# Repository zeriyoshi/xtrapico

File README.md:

# xtrapico
Double sided extra small footprint RP2040 implementation, Forcus on [JLCPCB](https://jlcpcb.com/).

Schma based by [22008-RP2040-Dev-Board](https://github.com/Breadstick-Innovations/22008-RP2040-Dev-Board)

# License
MIT

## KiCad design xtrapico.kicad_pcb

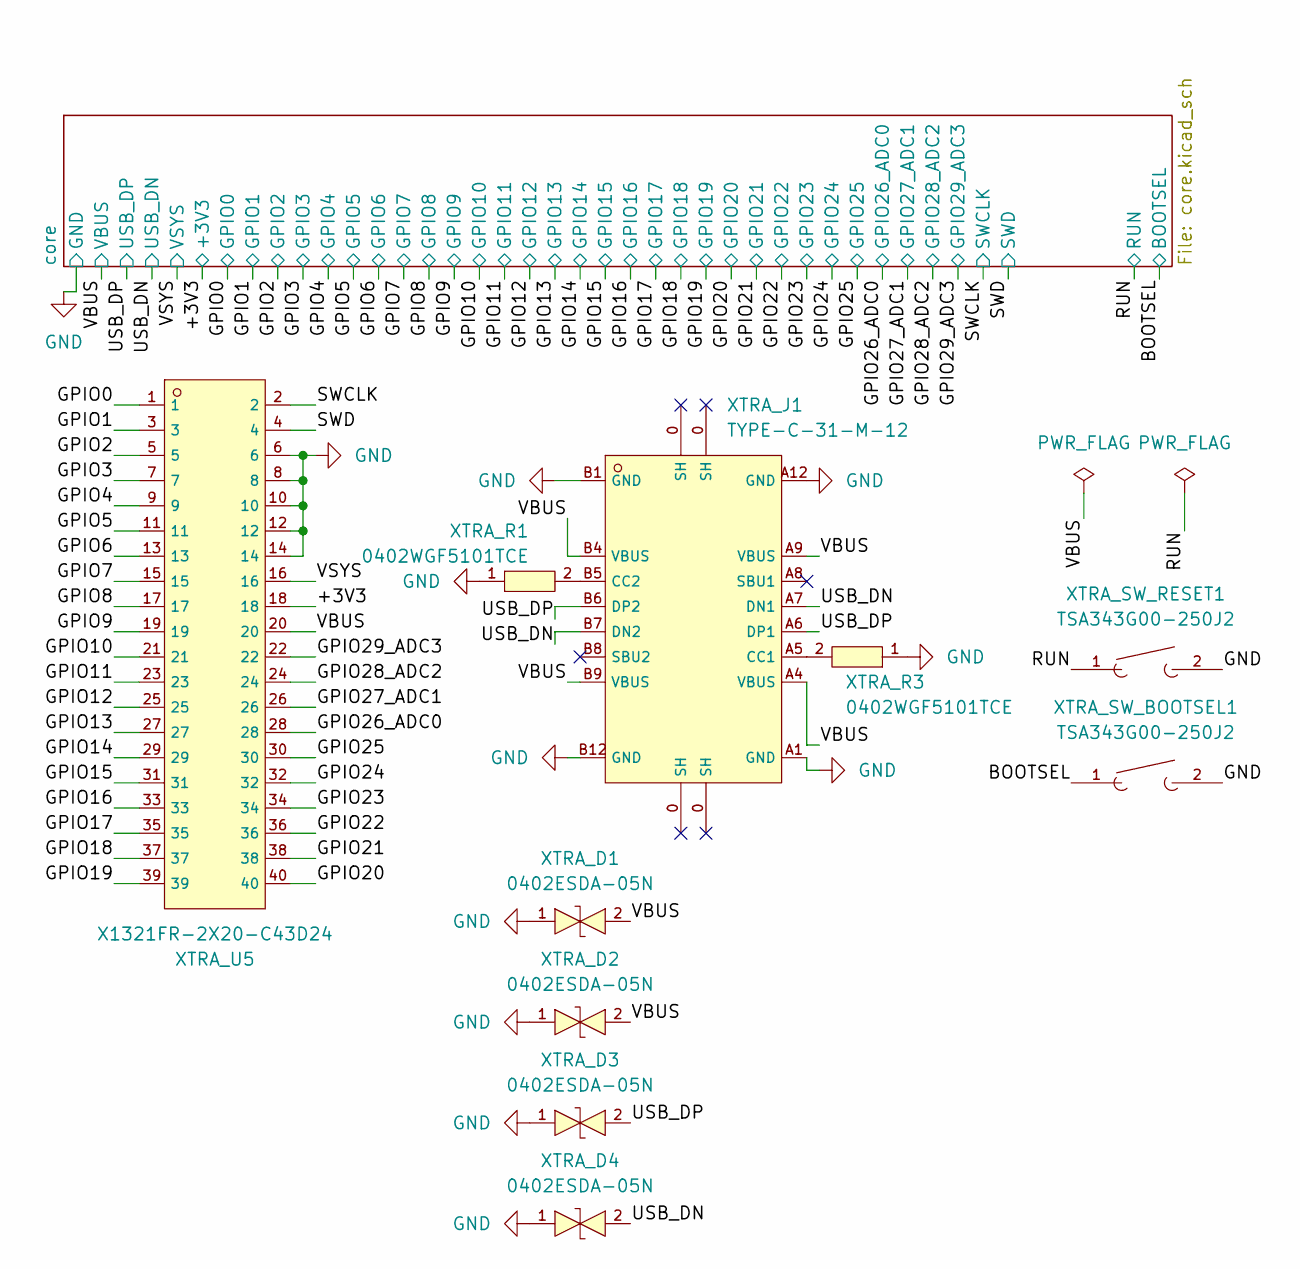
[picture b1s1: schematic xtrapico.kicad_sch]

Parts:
XTRA_D1, XTRA_D2, XTRA_D3, XTRA_D4: 0402ESDA-05N; D0402-BI; LCSC C316049
XTRA_J1: TYPE-C-31-M-12; USB-C_SMD-TYPE-C-31-M-12; LCSC C165948
XTRA_R1, XTRA_R3: 0402WGF5101TCE; R0402; LCSC C25905
XTRA_SW_BOOTSEL1: TSA343G00-250J2; SW-SMD_L4.0-W2.9-LS5.0; LCSC C354946
XTRA_SW_RESET1: TSA343G00-250J2; SW-SMD_L4.0-W2.9-LS5.0; LCSC C354946
XTRA_U5: X1321FR-2X20-C43D24; CONN-TH_40P_X1321FR-2X20-C43D24; LCSC C2881906

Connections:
/+3V3: XTRA_U5.18; also elsewhere on the board
/BOOTSEL: XTRA_SW_BOOTSEL1.1; also elsewhere on the board
/GPIO0: XTRA_U5.1; also elsewhere on the board
/GPIO1: XTRA_U5.3; also elsewhere on the board
/GPIO2: XTRA_U5.5; also elsewhere on the board
/GPIO3: XTRA_U5.7; also elsewhere on the board
/GPIO4: XTRA_U5.9; also elsewhere on the board
/GPIO5: XTRA_U5.11; also elsewhere on the board
/GPIO6: XTRA_U5.13; also elsewhere on the board
/GPIO7: XTRA_U5.15; also elsewhere on the board
/GPIO8: XTRA_U5.17; also elsewhere on the board
/GPIO9: XTRA_U5.19; also elsewhere on the board
/GPIO10: XTRA_U5.21; also elsewhere on the board
/GPIO11: XTRA_U5.23; also elsewhere on the board
/GPIO12: XTRA_U5.25; also elsewhere on the board
/GPIO13: XTRA_U5.27; also elsewhere on the board
/GPIO14: XTRA_U5.29; also elsewhere on the board
/GPIO15: XTRA_U5.31; also elsewhere on the board
/GPIO16: XTRA_U5.33; also elsewhere on the board
/GPIO17: XTRA_U5.35; also elsewhere on the board
/GPIO18: XTRA_U5.37; also elsewhere on the board
/GPIO19: XTRA_U5.39; also elsewhere on the board
/GPIO20: XTRA_U5.40; also elsewhere on the board
/GPIO21: XTRA_U5.38; also elsewhere on the board
/GPIO22: XTRA_U5.36; also elsewhere on the board
/GPIO23: XTRA_U5.34; also elsewhere on the board
/GPIO24: XTRA_U5.32; also elsewhere on the board
/GPIO25: XTRA_U5.30; also elsewhere on the board
/GPIO26_ADC0: XTRA_U5.28; also elsewhere on the board
/GPIO27_ADC1: XTRA_U5.26; also elsewhere on the board
/GPIO28_ADC2: XTRA_U5.24; also elsewhere on the board
/GPIO29_ADC3: XTRA_U5.22; also elsewhere on the board
/RUN: XTRA_SW_RESET1.1; also elsewhere on the board
/SWCLK: XTRA_U5.2; also elsewhere on the board
/SWD: XTRA_U5.4; also elsewhere on the board
/USB_DN: XTRA_D4.2, XTRA_J1.A7 (DN1), XTRA_J1.B7 (DN2); also elsewhere on the board
/USB_DP: XTRA_D3.2, XTRA_J1.A6 (DP1), XTRA_J1.B6 (DP2); also elsewhere on the board
/VBUS: XTRA_D1.2, XTRA_D2.2, XTRA_J1.A4 (VBUS), XTRA_J1.A9 (VBUS), XTRA_J1.B4 (VBUS), XTRA_J1.B9 (VBUS), XTRA_U5.20; also elsewhere on the board
/VSYS: XTRA_U5.16; also elsewhere on the board
GND: XTRA_D1.1, XTRA_D2.1, XTRA_D3.1, XTRA_D4.1, XTRA_J1.A1 (GND), XTRA_J1.A12 (GND), XTRA_J1.B1 (GND), XTRA_J1.B12 (GND), XTRA_R1.1, XTRA_R3.1, XTRA_SW_BOOTSEL1.2, XTRA_SW_RESET1.2, XTRA_U5.6, XTRA_U5.8, XTRA_U5.10, XTRA_U5.12, XTRA_U5.14; also elsewhere on the board
unnamed: XTRA_J1.A5 (CC1), XTRA_R3.2
unnamed: XTRA_J1.B5 (CC2), XTRA_R1.2

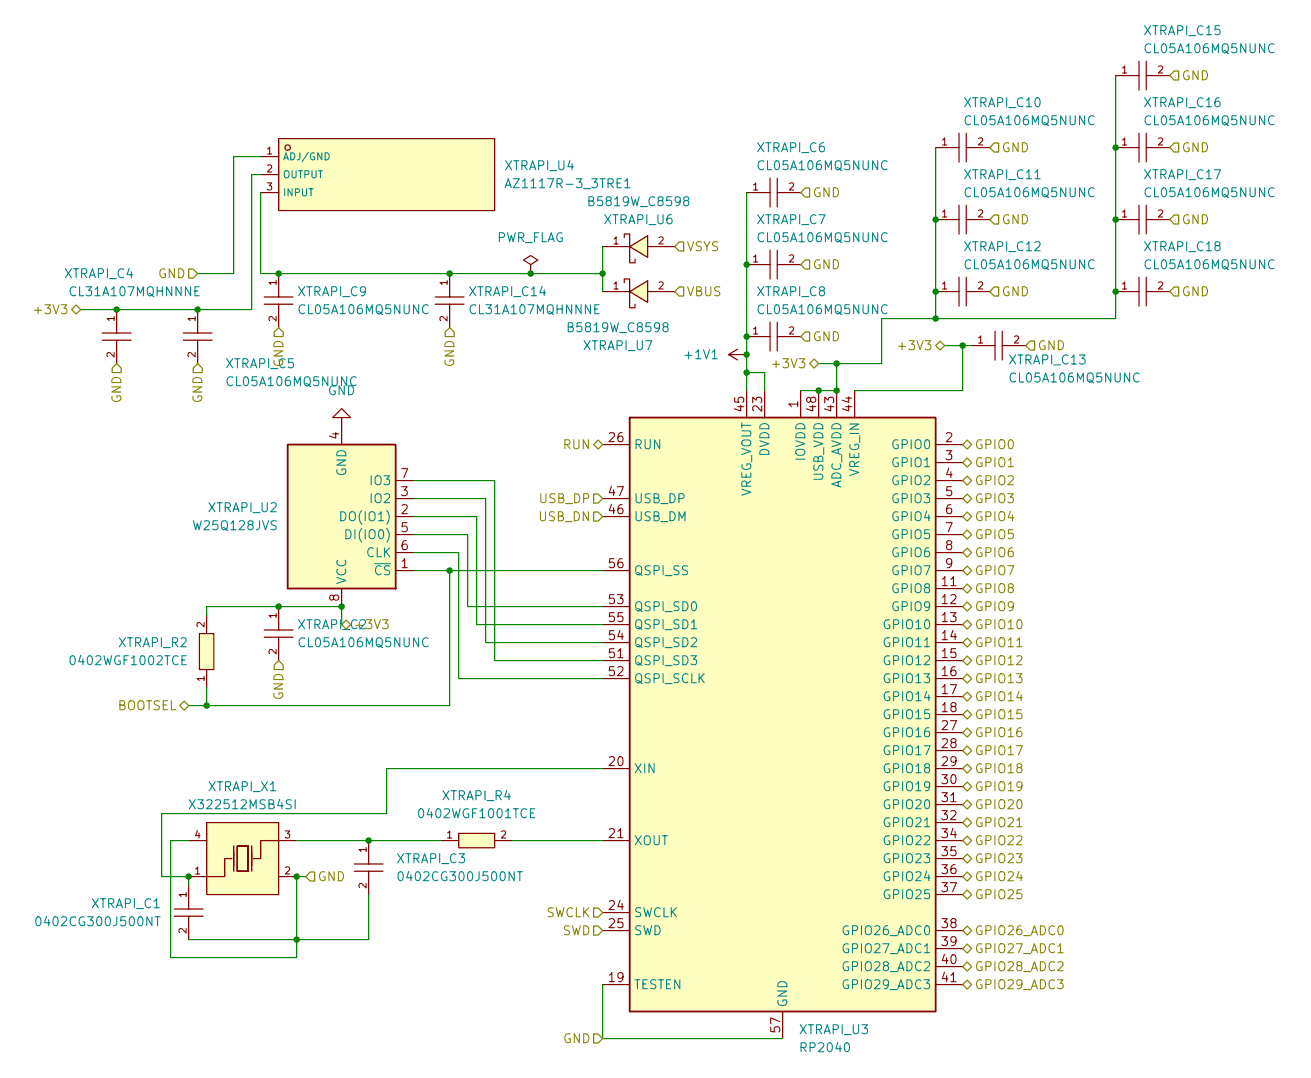
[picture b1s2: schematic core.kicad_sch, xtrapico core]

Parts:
XTRAPI_C1, XTRAPI_C3: 0402CG300J500NT; C0402; LCSC C1570
XTRAPI_C2, XTRAPI_C5, XTRAPI_C6, XTRAPI_C7, XTRAPI_C8, XTRAPI_C9, XTRAPI_C10, XTRAPI_C11, XTRAPI_C12, XTRAPI_C13, XTRAPI_C15, XTRAPI_C16, XTRAPI_C17, XTRAPI_C18: CL05A106MQ5NUNC; C0402; LCSC C15525
XTRAPI_C4, XTRAPI_C14: CL31A107MQHNNNE; C1206; LCSC C15008
XTRAPI_R2: 0402WGF1002TCE; R0402; LCSC C25744
XTRAPI_R4: 0402WGF1001TCE; R0402; LCSC C11702
XTRAPI_U2: W25Q128JVS; SOIC-8_5.23x5.23mm_P1.27mm
XTRAPI_U3: RP2040; QFN-56-1EP_7x7mm_P0.4mm_EP3.2x3.2mm
XTRAPI_U4: AZ1117R-3_3TRE1; SOT-89-3_L4.5-W2.5-P1.50-LS4.2-BR; LCSC C108493
XTRAPI_U6, XTRAPI_U7: B5819W_C8598; SOD-123_L2.7-W1.6-LS3.7-RD-1; LCSC C8598
XTRAPI_X1: X322512MSB4SI; OSC-SMD_4P-L3.2-W2.5-BL; LCSC C9002

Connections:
+1V1: XTRAPI_C6.1, XTRAPI_C7.1, XTRAPI_C8.1, XTRAPI_U3.23 (DVDD), XTRAPI_U3.45 (VREG_VOUT), XTRAPI_U3.50 (DVDD)
/+3V3: XTRAPI_C2.1, XTRAPI_C4.1, XTRAPI_C5.1, XTRAPI_C10.1, XTRAPI_C11.1, XTRAPI_C12.1, XTRAPI_C13.1, XTRAPI_C15.1, XTRAPI_C16.1, XTRAPI_C17.1, XTRAPI_C18.1, XTRAPI_R2.2, XTRAPI_U2.8 (VCC), XTRAPI_U3.1 (IOVDD), XTRAPI_U3.10 (IOVDD), XTRAPI_U3.22 (IOVDD), XTRAPI_U3.33 (IOVDD), XTRAPI_U3.42 (IOVDD), XTRAPI_U3.43 (ADC_AVDD), XTRAPI_U3.44 (VREG_IN), XTRAPI_U3.48 (USB_VDD), XTRAPI_U3.49 (IOVDD), XTRAPI_U4.2 (OUTPUT); also elsewhere on the board
/BOOTSEL: XTRAPI_R2.1, XTRAPI_U2.1 (~CS), XTRAPI_U3.56 (QSPI_SS); also elsewhere on the board
/GPIO0: XTRAPI_U3.2 (GPIO0); also elsewhere on the board
/GPIO1: XTRAPI_U3.3 (GPIO1); also elsewhere on the board
/GPIO2: XTRAPI_U3.4 (GPIO2); also elsewhere on the board
/GPIO3: XTRAPI_U3.5 (GPIO3); also elsewhere on the board
/GPIO4: XTRAPI_U3.6 (GPIO4); also elsewhere on the board
/GPIO5: XTRAPI_U3.7 (GPIO5); also elsewhere on the board
/GPIO6: XTRAPI_U3.8 (GPIO6); also elsewhere on the board
/GPIO7: XTRAPI_U3.9 (GPIO7); also elsewhere on the board
/GPIO8: XTRAPI_U3.11 (GPIO8); also elsewhere on the board
/GPIO9: XTRAPI_U3.12 (GPIO9); also elsewhere on the board
/GPIO10: XTRAPI_U3.13 (GPIO10); also elsewhere on the board
/GPIO11: XTRAPI_U3.14 (GPIO11); also elsewhere on the board
/GPIO12: XTRAPI_U3.15 (GPIO12); also elsewhere on the board
/GPIO13: XTRAPI_U3.16 (GPIO13); also elsewhere on the board
/GPIO14: XTRAPI_U3.17 (GPIO14); also elsewhere on the board
/GPIO15: XTRAPI_U3.18 (GPIO15); also elsewhere on the board
/GPIO16: XTRAPI_U3.27 (GPIO16); also elsewhere on the board
/GPIO17: XTRAPI_U3.28 (GPIO17); also elsewhere on the board
/GPIO18: XTRAPI_U3.29 (GPIO18); also elsewhere on the board
/GPIO19: XTRAPI_U3.30 (GPIO19); also elsewhere on the board
/GPIO20: XTRAPI_U3.31 (GPIO20); also elsewhere on the board
/GPIO21: XTRAPI_U3.32 (GPIO21); also elsewhere on the board
/GPIO22: XTRAPI_U3.34 (GPIO22); also elsewhere on the board
/GPIO23: XTRAPI_U3.35 (GPIO23); also elsewhere on the board
/GPIO24: XTRAPI_U3.36 (GPIO24); also elsewhere on the board
/GPIO25: XTRAPI_U3.37 (GPIO25); also elsewhere on the board
/GPIO26_ADC0: XTRAPI_U3.38 (GPIO26_ADC0); also elsewhere on the board
/GPIO27_ADC1: XTRAPI_U3.39 (GPIO27_ADC1); also elsewhere on the board
/GPIO28_ADC2: XTRAPI_U3.40 (GPIO28_ADC2); also elsewhere on the board
/GPIO29_ADC3: XTRAPI_U3.41 (GPIO29_ADC3); also elsewhere on the board
/RUN: XTRAPI_U3.26 (RUN); also elsewhere on the board
/SWCLK: XTRAPI_U3.24 (SWCLK); also elsewhere on the board
/SWD: XTRAPI_U3.25 (SWD); also elsewhere on the board
/USB_DN: XTRAPI_U3.46 (USB_DM); also elsewhere on the board
/USB_DP: XTRAPI_U3.47 (USB_DP); also elsewhere on the board
/VBUS: XTRAPI_U7.2 (+); also elsewhere on the board
/VSYS: XTRAPI_U6.2 (+); also elsewhere on the board
GND: XTRAPI_C1.2, XTRAPI_C2.2, XTRAPI_C3.2, XTRAPI_C4.2, XTRAPI_C5.2, XTRAPI_C6.2, XTRAPI_C7.2, XTRAPI_C8.2, XTRAPI_C9.2, XTRAPI_C10.2, XTRAPI_C11.2, XTRAPI_C12.2, XTRAPI_C13.2, XTRAPI_C14.2, XTRAPI_C15.2, XTRAPI_C16.2, XTRAPI_C17.2, XTRAPI_C18.2, XTRAPI_U2.4 (GND), XTRAPI_U3.19 (TESTEN), XTRAPI_U3.57 (GND), XTRAPI_U4.1 (ADJ/GND), XTRAPI_X1.2 (GND), XTRAPI_X1.4 (GND); also elsewhere on the board
unnamed: XTRAPI_U2.6 (CLK), XTRAPI_U3.52 (QSPI_SCLK)
unnamed: XTRAPI_U2.5 (DI(IO0)), XTRAPI_U3.53 (QSPI_SD0)
unnamed: XTRAPI_U2.2 (DO(IO1)), XTRAPI_U3.55 (QSPI_SD1)
unnamed: XTRAPI_U2.3 (IO2), XTRAPI_U3.54 (QSPI_SD2)
unnamed: XTRAPI_U2.7 (IO3), XTRAPI_U3.51 (QSPI_SD3)
unnamed: XTRAPI_C1.1, XTRAPI_U3.20 (XIN), XTRAPI_X1.1 (OSC1)
unnamed: XTRAPI_R4.2, XTRAPI_U3.21 (XOUT)
unnamed: XTRAPI_C9.1, XTRAPI_C14.1, XTRAPI_U4.3 (INPUT), XTRAPI_U6.1 (-), XTRAPI_U7.1 (-)
unnamed: XTRAPI_C3.1, XTRAPI_R4.1, XTRAPI_X1.3 (OSC2)

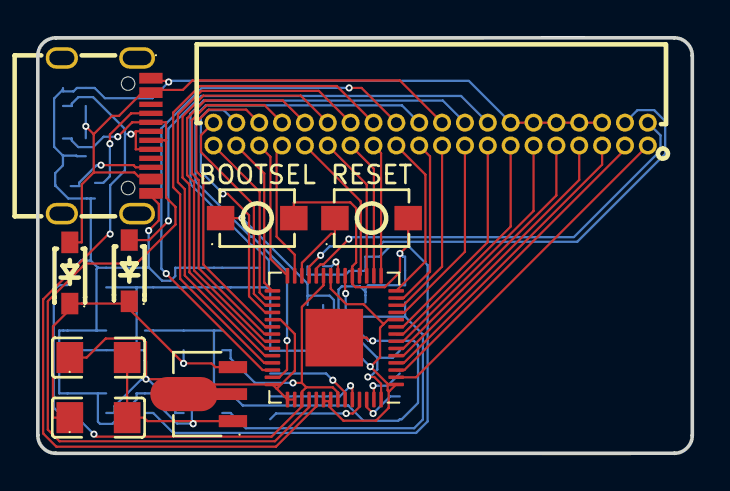
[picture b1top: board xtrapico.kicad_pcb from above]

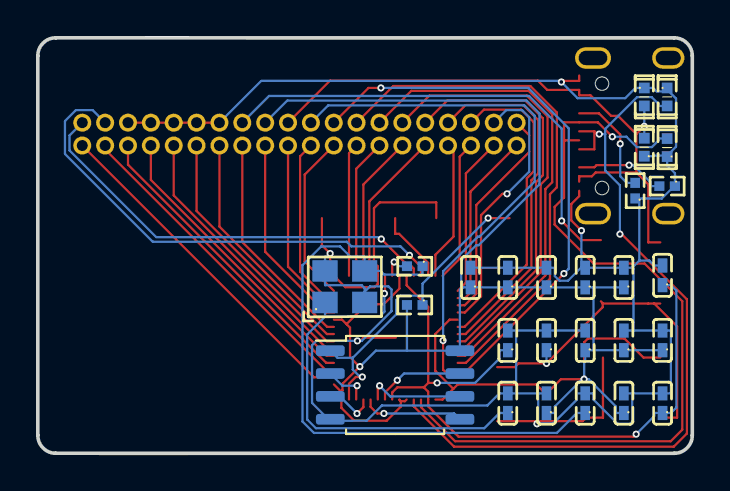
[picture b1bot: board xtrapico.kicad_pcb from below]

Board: 2 copper layers, 36.4 x 23.1 mm, 36 parts (26 on the bottom side), 52 nets.

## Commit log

2024-02-09 prepare release
